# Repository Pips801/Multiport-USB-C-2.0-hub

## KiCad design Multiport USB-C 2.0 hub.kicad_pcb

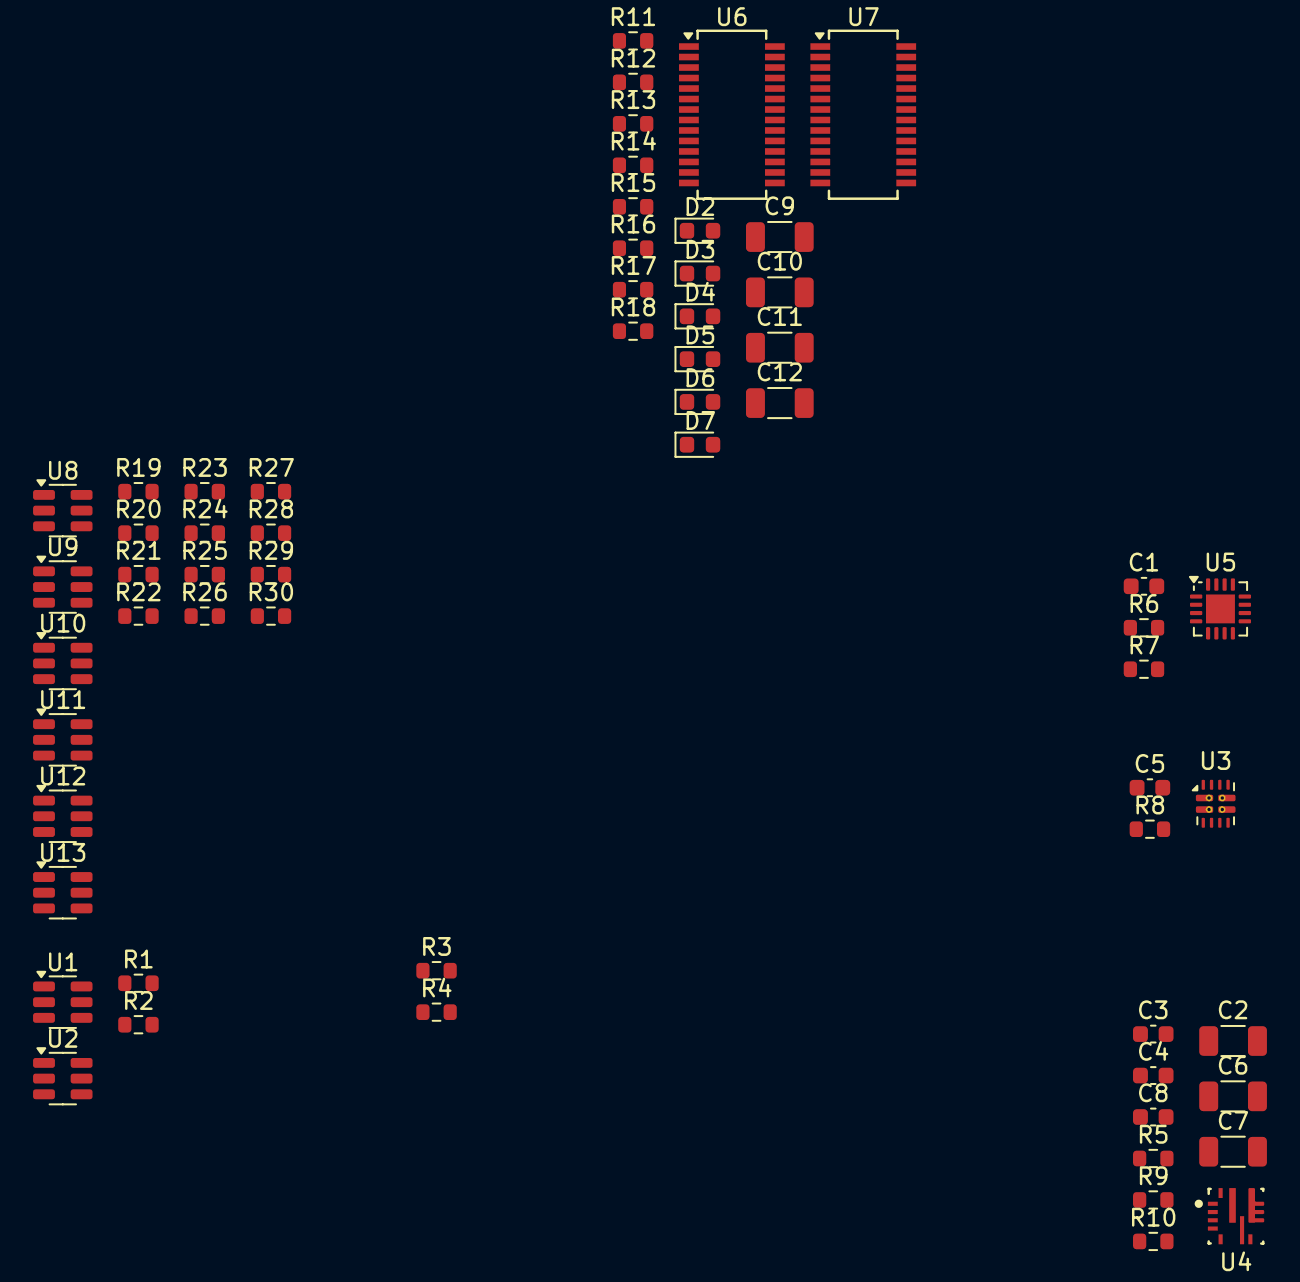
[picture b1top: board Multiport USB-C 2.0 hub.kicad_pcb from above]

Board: 2 copper layers, 61 parts (0 on the bottom side), 66 nets, no tracks yet.

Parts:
C1: 1μF; C_0603_1608Metric
C2, C9, C10, C11, C12: 10μF; C_1206_3216Metric
C3, C4, C5: 0.1μF; C_0603_1608Metric
C6, C7: 22μF; C_1206_3216Metric
C8: 47nF; C_0603_1608Metric
D2: DFP1; LED_0603_1608Metric
D3: DFP4; LED_0603_1608Metric
D4: DFP2; LED_0603_1608Metric
D5: DFP5; LED_0603_1608Metric
D6: DFP3; LED_0603_1608Metric
D7: DFP6; LED_0603_1608Metric
R1, R2: 5.1kΩ; R_0603_1608Metric
R3, R4: R_0603_1608Metric
R5: 73.2kΩ; R_0603_1608Metric
R6: 19kΩ; R_0603_1608Metric
R7: 21kΩ; R_0603_1608Metric
R8: 30kΩ; R_0603_1608Metric
R9: 10kΩ; R_0603_1608Metric
R10: 52.3kΩ; R_0603_1608Metric
R11, R12, R13, R14, R15, R16: ?Ω; R_0603_1608Metric
R17, R18: 2.7kΩ; R_0603_1608Metric
R19, R20, R21, R22, R23, R24, R25, R26, R27, R28, R29, R30: 22kΩ; R_0603_1608Metric
U1, U2, U8, U9, U10, U11, U12, U13: SRV05-4; SOT-23-6
U3: TPS2121; Texas_VQFN-HR-12_2x2.5mm_P0.5mm_ThermalVias
U4: TPS56A37RPAR; TPS56A37
U5: HUSB238A-xxxxx-QN16R; WQFN-16-1EP_3x3mm_P0.5mm_EP1.75x1.75mm
U6: FE1.1s HUB1; SSOP-28_3.9x9.9mm_P0.635mm
U7: FE1.1s HUB2; SSOP-28_3.9x9.9mm_P0.635mm

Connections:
/Downstream-facing ports/DFP1_D+: U6.11 (DP1), U8.3 (IO2)
/Downstream-facing ports/DFP1_D-: U6.10 (DM1), U8.1 (IO1)
/Downstream-facing ports/DFP2_D+: U6.9 (DP2), U9.3 (IO2)
/Downstream-facing ports/DFP2_D-: U6.8 (DM2), U9.1 (IO1)
/Downstream-facing ports/DFP3_D+: U6.7 (DP3), U10.3 (IO2)
/Downstream-facing ports/DFP3_D-: U6.6 (DM3), U10.1 (IO1)
/Downstream-facing ports/DFP4_D+: U7.11 (DP1), U11.3 (IO2)
/Downstream-facing ports/DFP4_D-: U7.10 (DM1), U11.1 (IO1)
/Downstream-facing ports/DFP5_D+: U7.9 (DP2), U12.3 (IO2)
/Downstream-facing ports/DFP5_D-: U7.8 (DM2), U12.1 (IO1)
/Downstream-facing ports/DFP6_D+: U7.7 (DP3), U13.3 (IO2)
/Downstream-facing ports/DFP6_D-: U7.6 (DM3), U13.1 (IO1)
/Downstream-facing ports/DFP_VBUS: C6.1, C7.1, R5.1, R19.1, R20.1, R21.1, R22.1, R23.1, R24.1, R25.1, R26.1, R27.1, R28.1, R29.1, R30.1, U6.18 (VBUSM), U6.20 (VDD5), U7.18 (VBUSM), U7.20 (VDD5), U8.5 (VP), U9.5 (VP), U10.5 (VP), U11.5 (VP), U12.5 (VP), U13.5 (VP)
/Downstream-facing ports/P1CC1: R19.2, U8.4 (IO3)
/Downstream-facing ports/P1CC2: R20.2, U8.6 (IO4)
/Downstream-facing ports/P2CC1: R21.2, U9.4 (IO3)
/Downstream-facing ports/P2CC2: R22.2, U9.6 (IO4)
/Downstream-facing ports/P3CC1: R23.2, U10.4 (IO3)
/Downstream-facing ports/P3CC2: R24.2, U10.6 (IO4)
/Downstream-facing ports/P4CC1: R25.2, U11.4 (IO3)
/Downstream-facing ports/P4CC2: R26.2, U11.6 (IO4)
/Downstream-facing ports/P5CC1: R27.2, U12.4 (IO3)
/Downstream-facing ports/P5CC2: R28.2, U12.6 (IO4)
/Downstream-facing ports/P6CC1: R29.2, U13.4 (IO3)
/Downstream-facing ports/P6CC2: R30.2, U13.6 (IO4)
/Power management/GATE: R4.2, U5.15 (GATE)
/Power management/PD_CC1: U1.1 (IO1), U5.3 (CC1)
/Power management/PD_CC2: U1.3 (IO2), U5.4 (CC2)
/Power management/PD_D+: U1.6 (IO4), U5.1 (D+)
/Power management/PD_D-: U1.4 (IO3), U5.2 (D-)
/Power management/PD_VBUS: C1.1, R3.1, U1.5 (VP), U5.16 (VBUS)
/Power management/UFP_VBUS: U2.5 (VP), U3.2 (IN2)
/Power management/VOUT: C2.1, C3.1, U3.1 (OUT), U3.8 (OUT), U4.1 (EN), U4.8 (VIN)
/USB hub/CHAIN_D+: U6.5 (DP4), U7.16 (DPU)
/USB hub/CHAIN_D-: U6.4 (DM4), U7.15 (DMU)
/USB hub/HUB1_DRV: D2.2 (A), D4.1 (K), D6.2 (A), U6.22 (DRV)
/USB hub/HUB1_LED1: R11.1, U6.23 (LED1/EESCL)
/USB hub/HUB1_LED2: R13.1, U6.24 (LED2)
/USB hub/HUB2_DRV: D3.2 (A), D5.1 (K), D7.2 (A), U7.22 (DRV)
/USB hub/HUB2_LED1: R12.1, U7.23 (LED1/EESCL)
/USB hub/HUB2_LED2: R14.1, U7.24 (LED2)
/USB hub/USB_D+: U2.6 (IO4), U6.16 (DPU)
/USB hub/USB_D-: U2.4 (IO3), U6.15 (DMU)
/Upstream-facing ports/CC1: R1.2, U2.1 (IO1)
/Upstream-facing ports/CC2: R2.1, U2.3 (IO2)
GND: C1.2, C2.2, C3.2, C5.2, C6.2, C7.2, C8.2, C9.1, C10.1, C11.1, C12.1, R1.1, R2.2, R6.2, R7.2, R8.2, R9.2, R10.2, R15.1, R16.1, R17.1, R18.1, U1.2 (VN), U2.2 (VN), U3.3 (CP2), U3.4 (OV2), U3.5 (OV1), U3.6 (PR1), U3.12 (GND), U4.3 (AGND), U4.9 (PGND), U5.12 (~EN), U5.17 (GND), U6.1 (VSS), U7.1 (VSS), U8.2 (VN), U9.2 (VN), U10.2 (VN), U11.2 (VN), U12.2 (VN), U13.2 (VN)
unnamed: R3.2, R4.1
unnamed: D2.1 (K), D4.2 (A), R11.2
unnamed: D3.1 (K), D5.2 (A), R12.2
unnamed: D6.1 (K), R13.2
unnamed: D7.1 (K), R14.2
unnamed: R8.1, U3.10 (ILIM)
unnamed: C5.1, U3.11 (SS)
unnamed: C4.1, U4.7 (BOOT)
unnamed: R5.2, R9.1, U4.2 (FB)
unnamed: R10.1, U4.10 (MODE)
unnamed: C8.1, U4.5 (SS)
unnamed: C4.2, U4.6 (SW)
unnamed: R7.1, U5.10 (SCL/SNK_ISET)
unnamed: R6.1, U5.9 (SDA/SNK_VSET)
unnamed: R17.2, U6.14 (REXT)
unnamed: C10.2, U6.12 (VD18_O), U6.28 (VD18)
unnamed: C9.2, U6.13 (VD33), U6.21 (VD33_O)
unnamed: R18.2, U7.14 (REXT)
unnamed: C12.2, U7.12 (VD18_O), U7.28 (VD18)
unnamed: C11.2, U7.13 (VD33), U7.21 (VD33_O)

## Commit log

2025-12-08 basic schematic layout
2025-12-09 add TPS56A37 and TPS2121
2025-12-11 good first pass
2025-12-11 more work on USB hubs
2025-12-11 Update DFPs
2025-12-15 footprints
